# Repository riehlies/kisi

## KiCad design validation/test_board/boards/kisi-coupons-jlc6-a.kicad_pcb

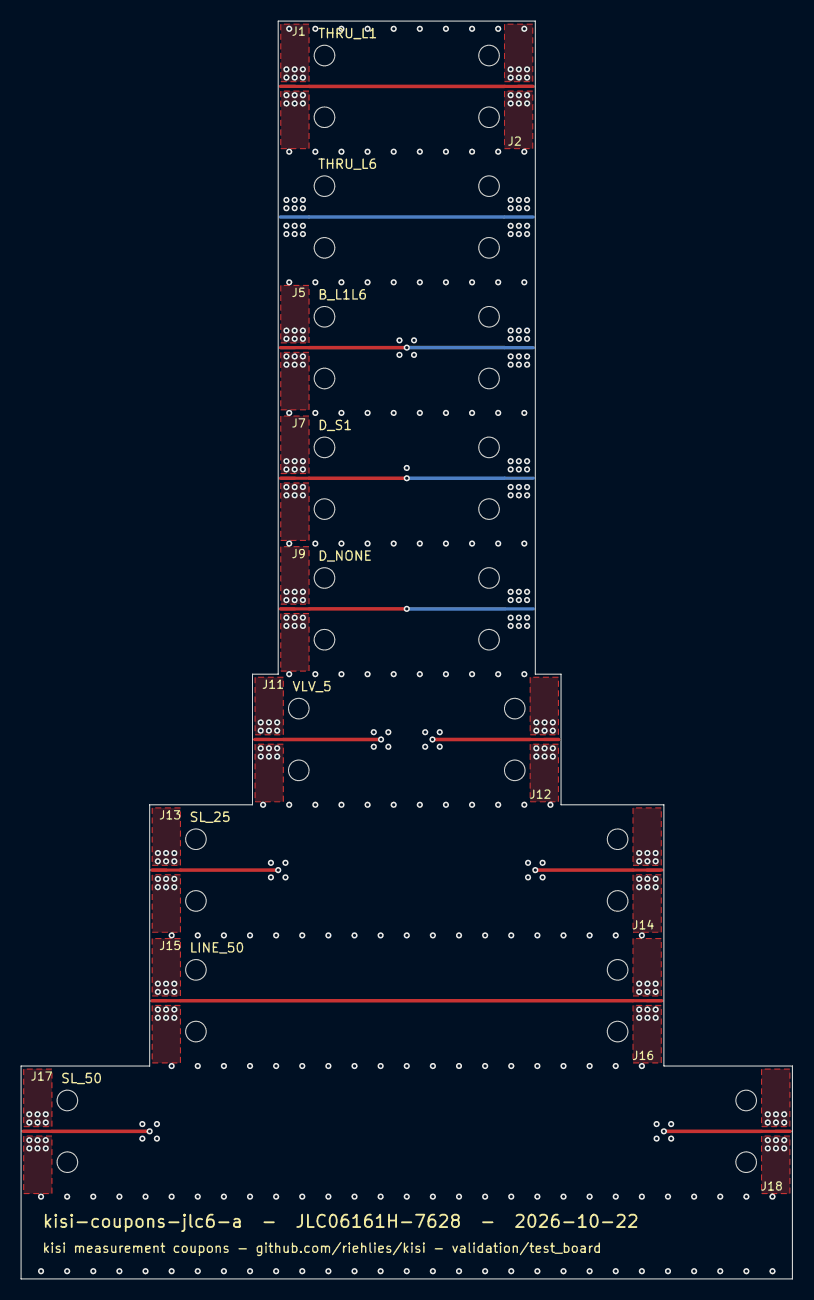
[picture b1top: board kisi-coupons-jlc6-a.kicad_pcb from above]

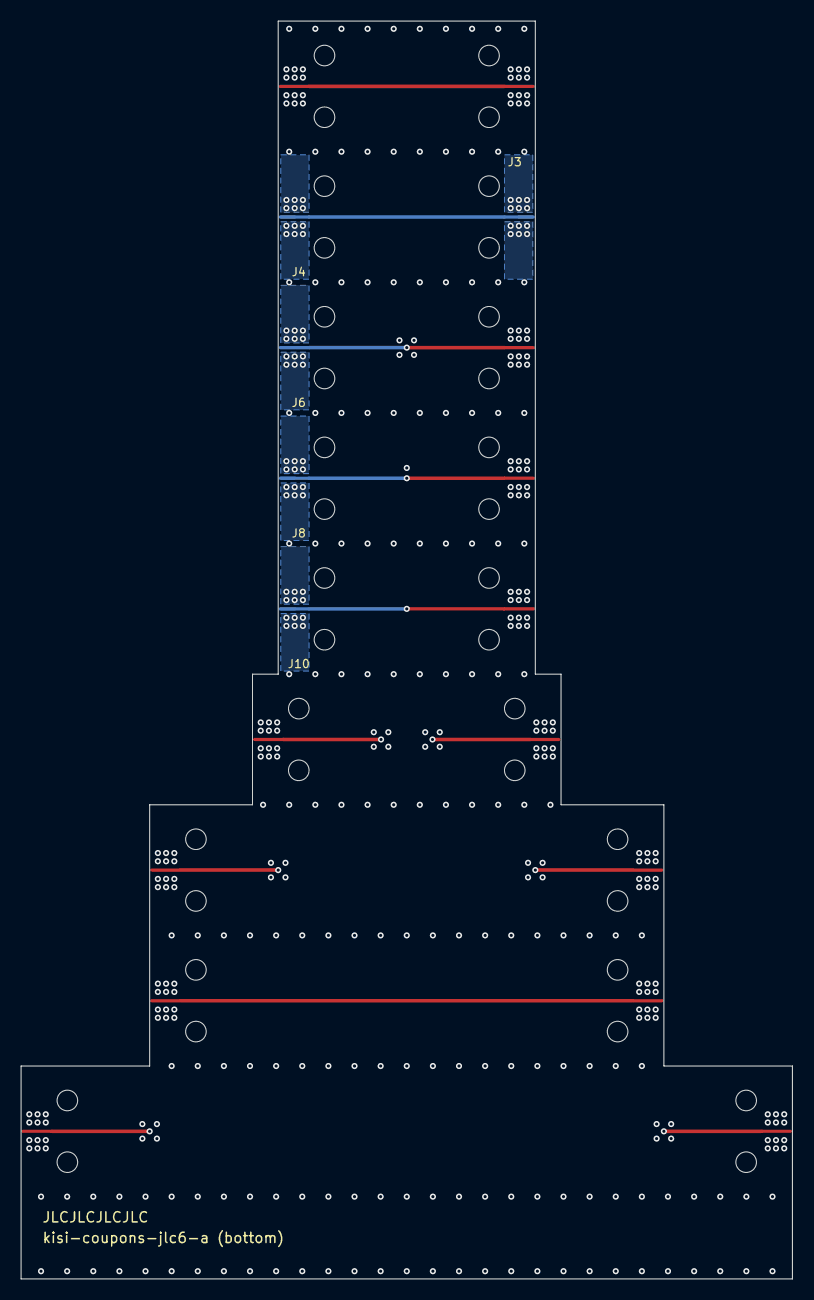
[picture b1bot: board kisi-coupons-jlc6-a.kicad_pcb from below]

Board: 6 copper layers, 75.0 x 122.3 mm, 18 parts (5 on the bottom side), 9 nets.

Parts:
J1, J2, J3, J4, J5, J6, J7, J8, J9, J10, J11, J12, J13, J14, J15, J16, J17, J18: 292-04A-14 / 1092-01A-14; SWM_EndLaunch_Narrow_PLACEHOLDER

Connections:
SE_B_L1L6: J5.1, J6.1
SE_D_NONE: J9.1, J10.1
SE_D_S1: J7.1, J8.1
SE_LINE_50: J15.1, J16.1
SE_SL_25: J13.1, J14.1
SE_SL_50: J17.1, J18.1
SE_THRU_L1: J1.1, J2.1
SE_THRU_L6: J3.1, J4.1
SE_VLV_5: J11.1, J12.1

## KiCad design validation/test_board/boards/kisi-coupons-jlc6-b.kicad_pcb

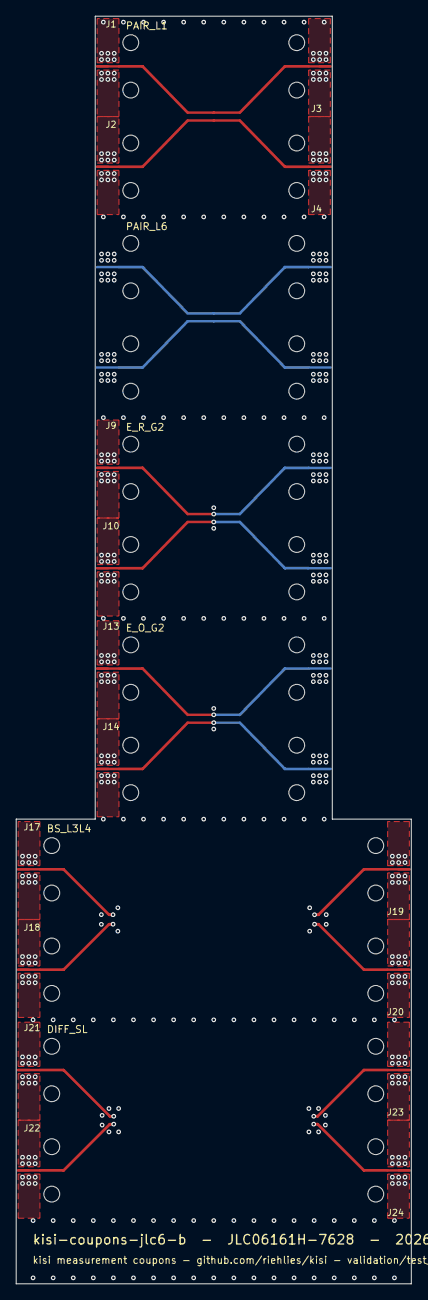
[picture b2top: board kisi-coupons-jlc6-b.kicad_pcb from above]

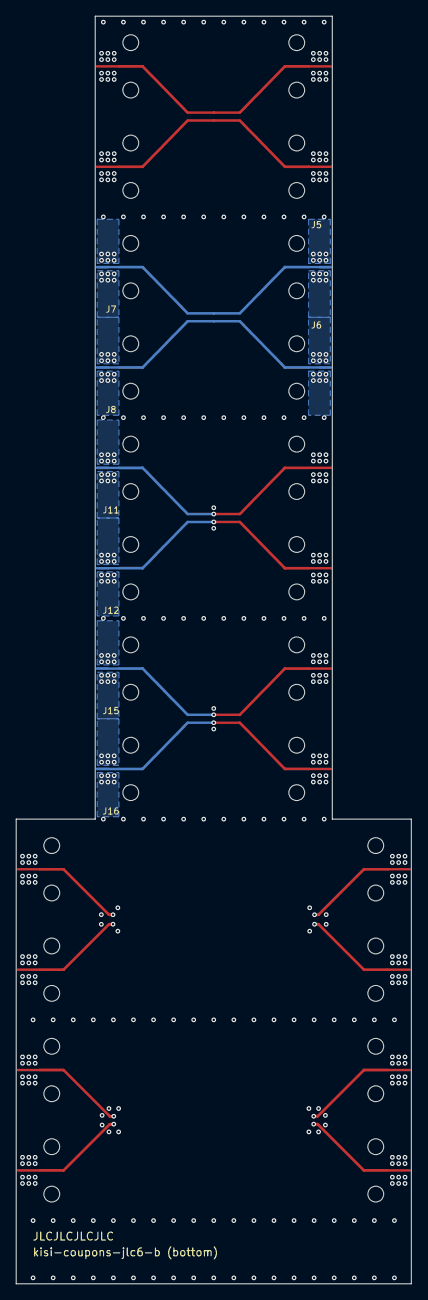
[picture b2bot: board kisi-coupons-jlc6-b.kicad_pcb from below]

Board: 6 copper layers, 50.0 x 160.4 mm, 24 parts (8 on the bottom side), 12 nets.

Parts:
J1, J2, J3, J4, J5, J6, J7, J8, J9, J10, J11, J12, J13, J14, J15, J16, J17, J18, J19, J20, J21, J22, J23, J24: 292-04A-14 / 1092-01A-14; SWM_EndLaunch_Narrow_PLACEHOLDER

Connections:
DP_DIFF_SL_N: J22.1, J24.1
DP_DIFF_SL_P: J21.1, J23.1
DP_E_O_G2_N: J14.1, J16.1
DP_E_O_G2_P: J13.1, J15.1
DP_E_R_G2_N: J10.1, J12.1
DP_E_R_G2_P: J9.1, J11.1
DP_PAIR_L1_N: J2.1, J4.1
DP_PAIR_L1_P: J1.1, J3.1
DP_PAIR_L6_N: J6.1, J8.1
DP_PAIR_L6_P: J5.1, J7.1
SE_BS_A: J17.1, J19.1
SE_BS_V: J18.1, J20.1

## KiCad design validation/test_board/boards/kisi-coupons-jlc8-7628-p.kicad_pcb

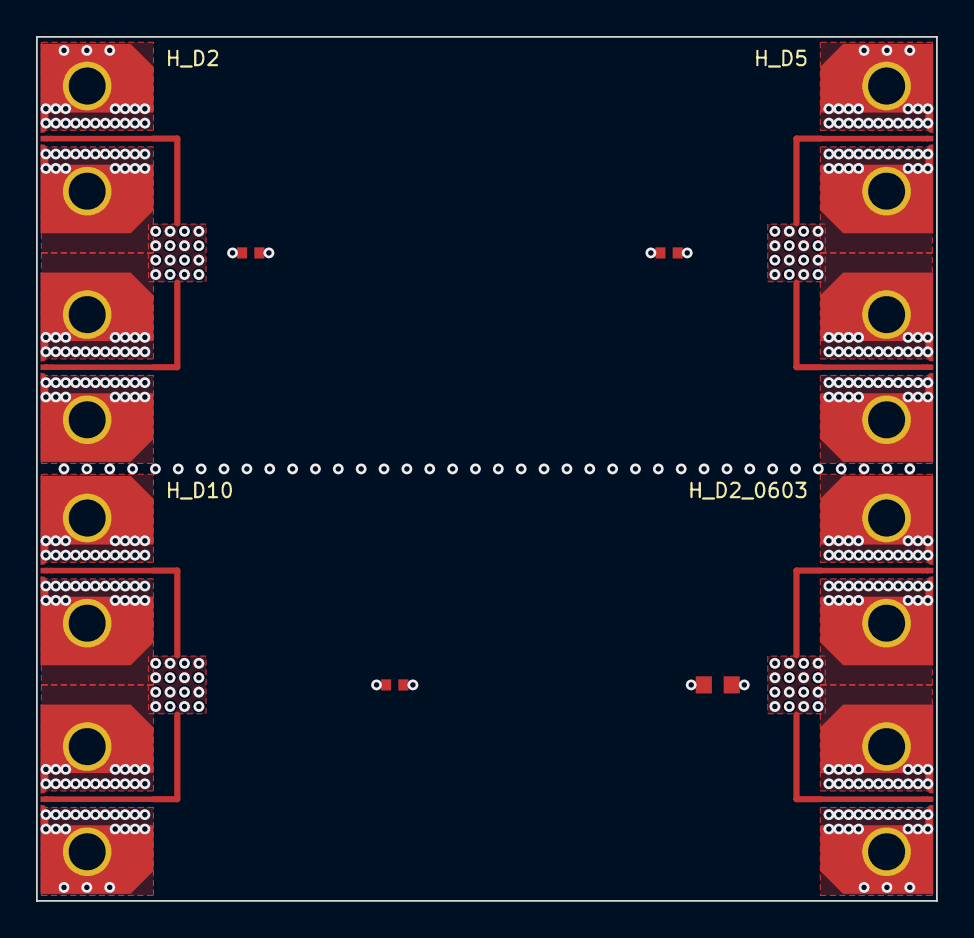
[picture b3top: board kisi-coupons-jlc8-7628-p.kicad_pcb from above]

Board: 8 copper layers, 50.0 x 48.0 mm, 16 parts (0 on the bottom side), 5 nets.

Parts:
C1, C2, C3: 100nF 16V X7R; C_0402_1005Metric
C4: 100nF 16V X7R; C_0603_1608Metric
J1, J2, J3, J4, J5, J6, J7, J8: 292-J-P-EP-ST-EL-01; Samtec_292-J-P-EP-ST-EL-01_EdgeLaunch_W0.315
U1: pin field (no part); U_VDD_H_D2
U2: pin field (no part); U_VDD_H_D5
U3: pin field (no part); U_VDD_H_D10
U4: pin field (no part); U_VDD_H_D2_0603

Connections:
GND: C1.1, C2.2, C3.1, C4.2, J1.2, J1.3, J2.2, J2.3, J3.2, J3.3, J4.2, J4.3, J5.2, J5.3, J6.2, J6.3, J7.2, J7.3, J8.2, J8.3, U1.A2, U1.A4, U1.B1, U1.B3, U1.C2, U1.C4, U1.D1, U1.D3, U2.A2, U2.A4, U2.B1, U2.B3, U2.C2, U2.C4, U2.D1, U2.D3, U3.A2, U3.A4, U3.B1, U3.B3, U3.C2, U3.C4, U3.D1, U3.D3, U4.A2, U4.A4, U4.B1, U4.B3, U4.C2, U4.C4, U4.D1, U4.D3
VDD_H_D2: C1.2, J1.1, J2.1, U1.A1, U1.A3, U1.B2, U1.B4, U1.C1, U1.C3, U1.D2, U1.D4
VDD_H_D2_0603: C4.1, J7.1, J8.1, U4.A1, U4.A3, U4.B2, U4.B4, U4.C1, U4.C3, U4.D2, U4.D4
VDD_H_D5: C2.1, J3.1, J4.1, U2.A1, U2.A3, U2.B2, U2.B4, U2.C1, U2.C3, U2.D2, U2.D4
VDD_H_D10: C3.2, J5.1, J6.1, U3.A1, U3.A3, U3.B2, U3.B4, U3.C1, U3.C3, U3.D2, U3.D4
